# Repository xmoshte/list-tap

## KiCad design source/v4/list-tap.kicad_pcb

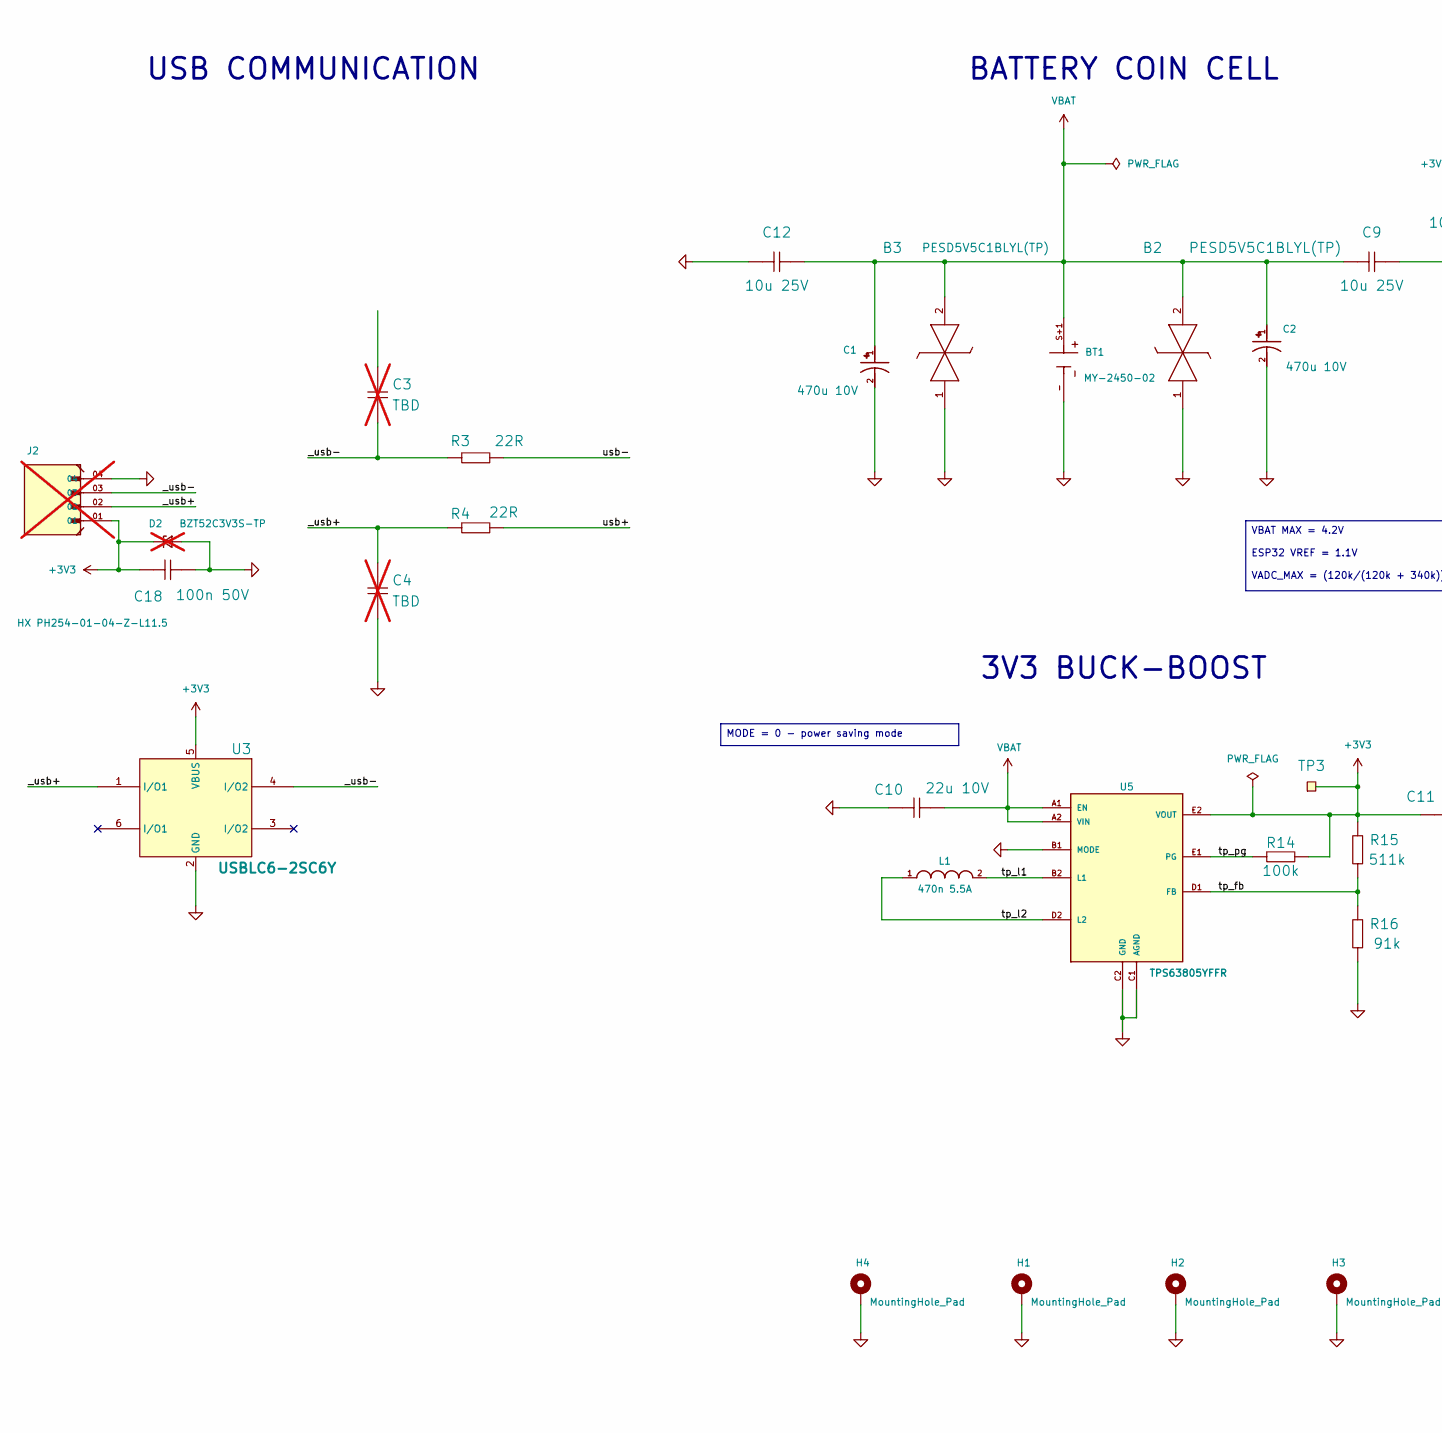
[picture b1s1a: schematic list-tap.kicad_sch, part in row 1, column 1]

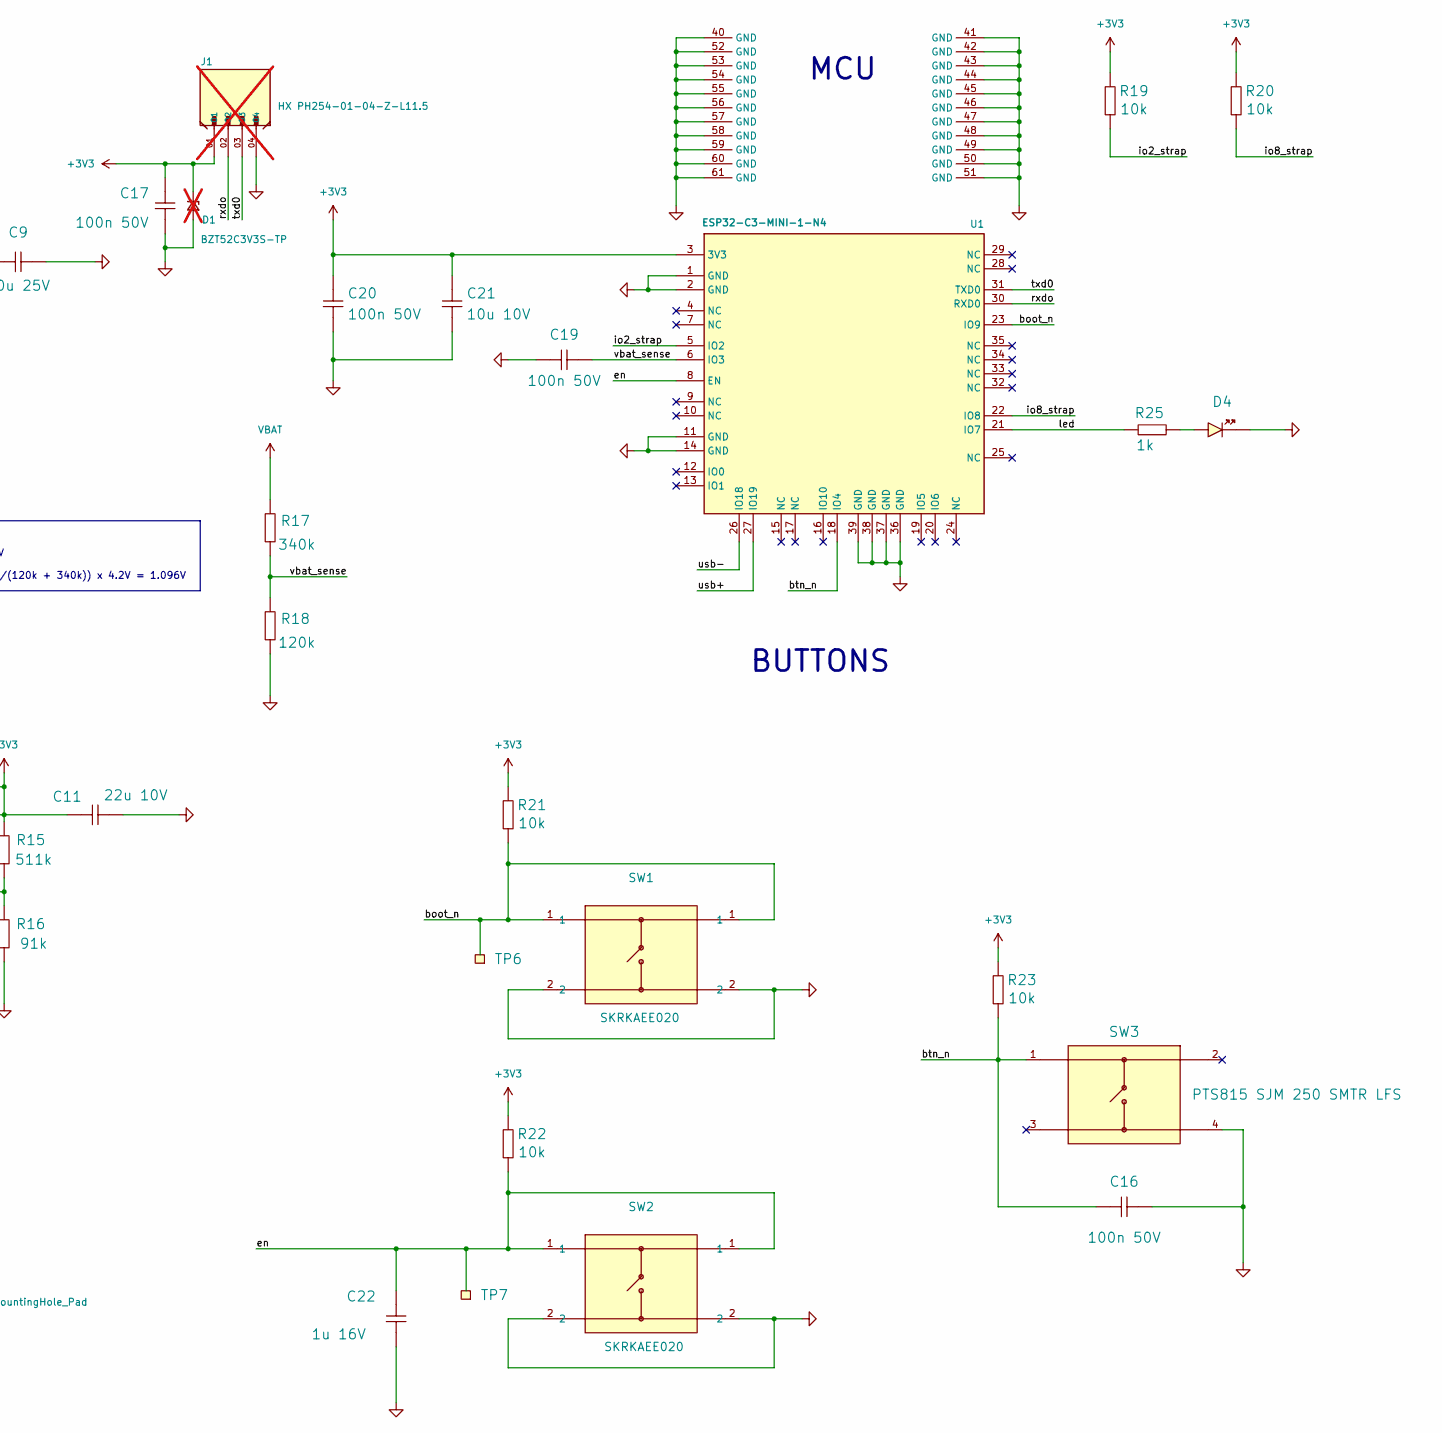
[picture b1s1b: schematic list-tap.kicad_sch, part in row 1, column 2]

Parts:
B2, B3: PESD5V5C1BLYL(TP); PESD5V5C1BLYL; Manufacturer Part Number PESD5V5C1BLYL(TP); LCSC Part # C54194967
BT1: MY-2450-02; BAT_BK-880; Manufacturer Part Number MY-2450-02; LCSC Part # C2979177
C1, C2: 470u 10V; PXTE010M477E060STU; Manufacturer Part Number PXTE010M477E060STU; LCSC Part # C724264
C3, C4: TBD; CAPC1005X04L; not fitted
C9, C12: 10u 25V; CAPC1608X06L; Manufacturer Part Number CL10A106MA8NRNC; LCSC Part # C96446
C10, C11: 22u 10V; CAPC1005X04L; Manufacturer Part Number CGA0402X5R226M100GT; LCSC Part # C6119813
C16, C17, C18, C19, C20: 100n 50V; CAPC1005X04L; Manufacturer Part Number CC0402X7R50V104MN; LCSC Part # C53084453
C21: 10u 10V; CAPC1005X04L; Manufacturer Part Number CL05A106MP5NUNC; LCSC Part # C315248
C22: 1u 16V; CAPC1005X04L; Manufacturer Part Number CL05A105KO5NNNC; LCSC Part # C29266
D1, D2: BZT52C3V3S-TP; SOD2512X115N; Manufacturer Part Number BZT52C3V3S-TP; LCSC Part # C668900; not fitted
D4: GREEN; LED_0402_GREEN; Manufacturer Part Number 16-213/GHC-YR1S1/3T; LCSC Part # C74338
H1, H2, H3, H4: MountingHole_Pad; MountingHole_2.2mm_M2_Pad_Via
J1, J2: HX PH254-01-04-Z-L11.5; Manufacturer Part Number HX PH254-01-04-Z-L11.5; LCSC Part # C52016392; not fitted
L1: 470n 5.5A; INDC2520X100N; Manufacturer Part Number PCT252010-R47-M; LCSC Part # C54557079
R3, R4: 22R; RESC1005X04L; Manufacturer Part Number RC0402FR-0722RL; LCSC Part # C114765
R14: 100k; RESC1005X04L; Manufacturer Part Number RC0402FR-07100KL; LCSC Part # C60491
R15: 511k; RESC1005X04L; Manufacturer Part Number 0402WGF5113TCE; LCSC Part # C64042
R16: 91k; RESC1005X04L; Manufacturer Part Number RT0402BRD0791KL; LCSC Part # C852952
R17: 340k; RESC1005X04L; Manufacturer Part Number FRC0402F3403TS; LCSC Part # C2933090
R18: 120k; RESC1005X04L; Manufacturer Part Number FRC0402F1203TS; LCSC Part # C2909314
R19, R20, R21, R22, R23: 10k; RESC1005X04L; Manufacturer Part Number RC0402FR-0710KL; LCSC Part # C60490
R25: 1k; RESC1005X04L; Manufacturer Part Number RC0402FR-071KL; LCSC Part # C106235
SW1, SW2: SKRKAEE020; SW2_SKRKAEE020_ALPS; Manufacturer Part Number SKRKAEE020; LCSC Part # C115357
SW3: PTS815 SJM 250 SMTR LFS; PTS815; Manufacturer Part Number PTS815 SJM 250 SMTR LFS; LCSC Part # C2689510
TP3, TP6, TP7: Test Point; TP_SMD_D1.5mm; Part Number TP_SMD_Ø1.5MM
U1: ESP32-C3-MINI-1-N4; ESP32C3MINI1N4; Manufacturer Part Number ESP32-C3-MINI-1-N4; LCSC Part # C2838502
U3: USBLC6-2SC6Y; SOT23-6L_STM; Manufacturer Part Number USBLC6-2SC6Y; LCSC Part # C2969755
U5: TPS63805YFFR; BGA15N40P5X3_225X134X62N; Manufacturer Part Number TPS63805YFFR; LCSC Part # C2879615

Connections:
+3V3: C11.1, C17.2, C18.2, C20.2, C21.2, D1.K, D2.K, J1.01, J2.01, R14.2, R15.2, R19.2, R20.2, R21.2, R22.2, R23.2, TP3.1 (1_1), U1.3 (3V3), U3.5 (VBUS), U5.E2 (VOUT), U5.E3 (VOUT)
/_usb+: C4.2, J2.02, R4.1, U3.1 (I/O1)
/_usb-: C3.1 (1_1), J2.03, R3.1, U3.4 (I/O2)
/boot_n: R21.1, SW1.1, TP6.1 (1_1), U1.23 (IO9)
/btn_n: C16.2, R23.1, SW3.1, U1.18 (IO4)
/en: C22.1, R22.1, SW2.1, TP7.1 (1_1), U1.8 (EN)
/io2_strap: R19.1, U1.5 (IO2)
/io8_strap: R20.1, U1.22 (IO8)
/led: R25.2, U1.21 (IO7)
/rxdo: J1.02, U1.30 (RXD0)
/tp_fb: R15.1, R16.2, U5.D1 (FB)
/tp_l1: L1.2, U5.B2 (L1), U5.B3 (L1)
/tp_l2: L1.1, U5.D2 (L2), U5.D3 (L2)
/tp_pg: R14.1, U5.E1 (PG)
/txd0: J1.03, U1.31 (TXD0)
/usb+: R4.2, U1.27 (IO19)
/usb-: R3.2, U1.26 (IO18)
/vbat_sense: C19.2, R17.1, R18.2, U1.6 (IO3)
GND: B2.1 (K1), B3.1 (K1), BT1.-, C1.2, C2.2, C4.1, C9.2, C10.1, C11.2, C12.2, C16.1, C17.1, C18.1, C19.1, C20.1, C21.1, C22.2, D1.A, D2.A, D4.K, H1.1 (1_1), H2.1 (1_1), H3.1 (1_1), H4.1 (1_1), J1.04, J2.04, R16.1, R18.1, SW1.2, SW2.2, SW3.4, U1.1 (GND), U1.2 (GND), U1.11 (GND), U1.14 (GND), U1.36 (GND), U1.37 (GND), U1.38 (GND), U1.39 (GND), U1.40 (GND), U1.41 (GND), U1.42 (GND), U1.43 (GND), U1.44 (GND), U1.45 (GND), U1.46 (GND), U1.47 (GND), U1.48 (GND), U1.49 (GND), U1.50 (GND), U1.51 (GND), U1.52 (GND), U1.53 (GND), U1.54 (GND), U1.55 (GND), U1.56 (GND), U1.57 (GND), U1.58 (GND), U1.59 (GND), U1.60 (GND), U1.61 (GND), U3.2 (GND), U5.B1 (MODE), U5.C1 (AGND), U5.C2 (GND), U5.C3 (GND)
unnamed: D4.A, R25.1
VBAT: B2.2 (K2), B3.2 (K2), BT1.S+1, BT1.S+2, C1.1, C2.1, C9.1, C10.2, C12.1, R17.2, U5.A1 (EN), U5.A2 (VIN), U5.A3 (VIN)

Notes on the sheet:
3V3 BUCK-BOOST
USB COMMUNICATION
MCU
BUTTONS
BATTERY COIN CELL
VBAT MAX = 4.2V ESP32 VREF = 1.1V VADC_MAX = (120k/(120k + 340k)) x 4.2V = 1.096V
MODE = 0 - power saving mode

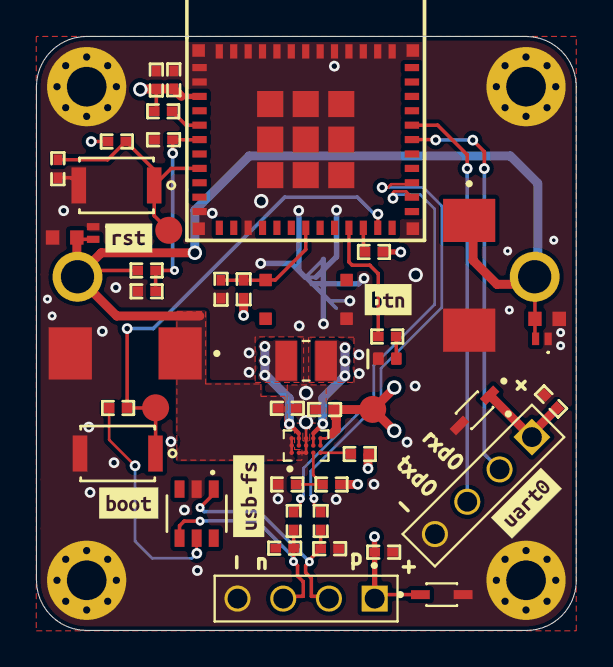
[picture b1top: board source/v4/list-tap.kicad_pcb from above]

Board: 2 copper layers, 30.0 x 33.0 mm, 55 parts (1 on the bottom side), 21 nets.

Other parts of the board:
kibuzzard-6AE057E3: G***; kibuzzard-6AE057E3
kibuzzard-6AE057F3: G***; kibuzzard-6AE057F3
kibuzzard-6AE0575D: G***; kibuzzard-6AE0575D
kibuzzard-6AE0576D: G***; kibuzzard-6AE0576D
kibuzzard-6AE0579C: G***; kibuzzard-6AE0579C

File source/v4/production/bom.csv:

Designator,Footprint,Quantity,Value,LCSC Part #
"B2, B3",PESD5V5C1BLYL,2,PESD5V5C1BLYL(TP),C54194967
BT1,BAT_BK-880,1,MY-2450-02,C2979177
"C1, C2",PXTE010M477E060STU,2,470u 10V,C724264
"C10, C11",CAPC1005X04L,2,22u 10V,C6119813
"C12, C9",CAPC1608X06L,2,10u 25V,C96446
"C16, C17, C18, C19, C20",CAPC1005X04L,5,100n 50V,C53084453
C21,CAPC1005X04L,1,10u 10V,C315248
C22,CAPC1005X04L,1,1u 16V,C29266
D4,LED_0402_GREEN,1,GREEN,C74338
L1,INDC2520X100N,1,470n 5.5A,C54557079
R14,RESC1005X04L,1,100k,C60491
R15,RESC1005X04L,1,511k,C64042
R16,RESC1005X04L,1,91k,C852952
R17,RESC1005X04L,1,340k,C2933090
R18,RESC1005X04L,1,120k,C2909314
"R19, R20, R21, R22, R23",RESC1005X04L,5,10k,C60490
R25,RESC1005X04L,1,1k,C106235
"R3, R4",RESC1005X04L,2,22R,C114765
"SW1, SW2",SW2_SKRKAEE020_ALPS,2,SKRKAEE020,C115357
SW3,PTS815,1,PTS815 SJM 250 SMTR LFS,C2689510
U1,ESP32C3MINI1N4,1,ESP32-C3-MINI-1-N4,C2838502
U3,SOT23-6L_STM,1,USBLC6-2SC6Y,C2969755
U5,BGA15N40P5X3_225X134X62N,1,TPS63805YFFR,C2879615

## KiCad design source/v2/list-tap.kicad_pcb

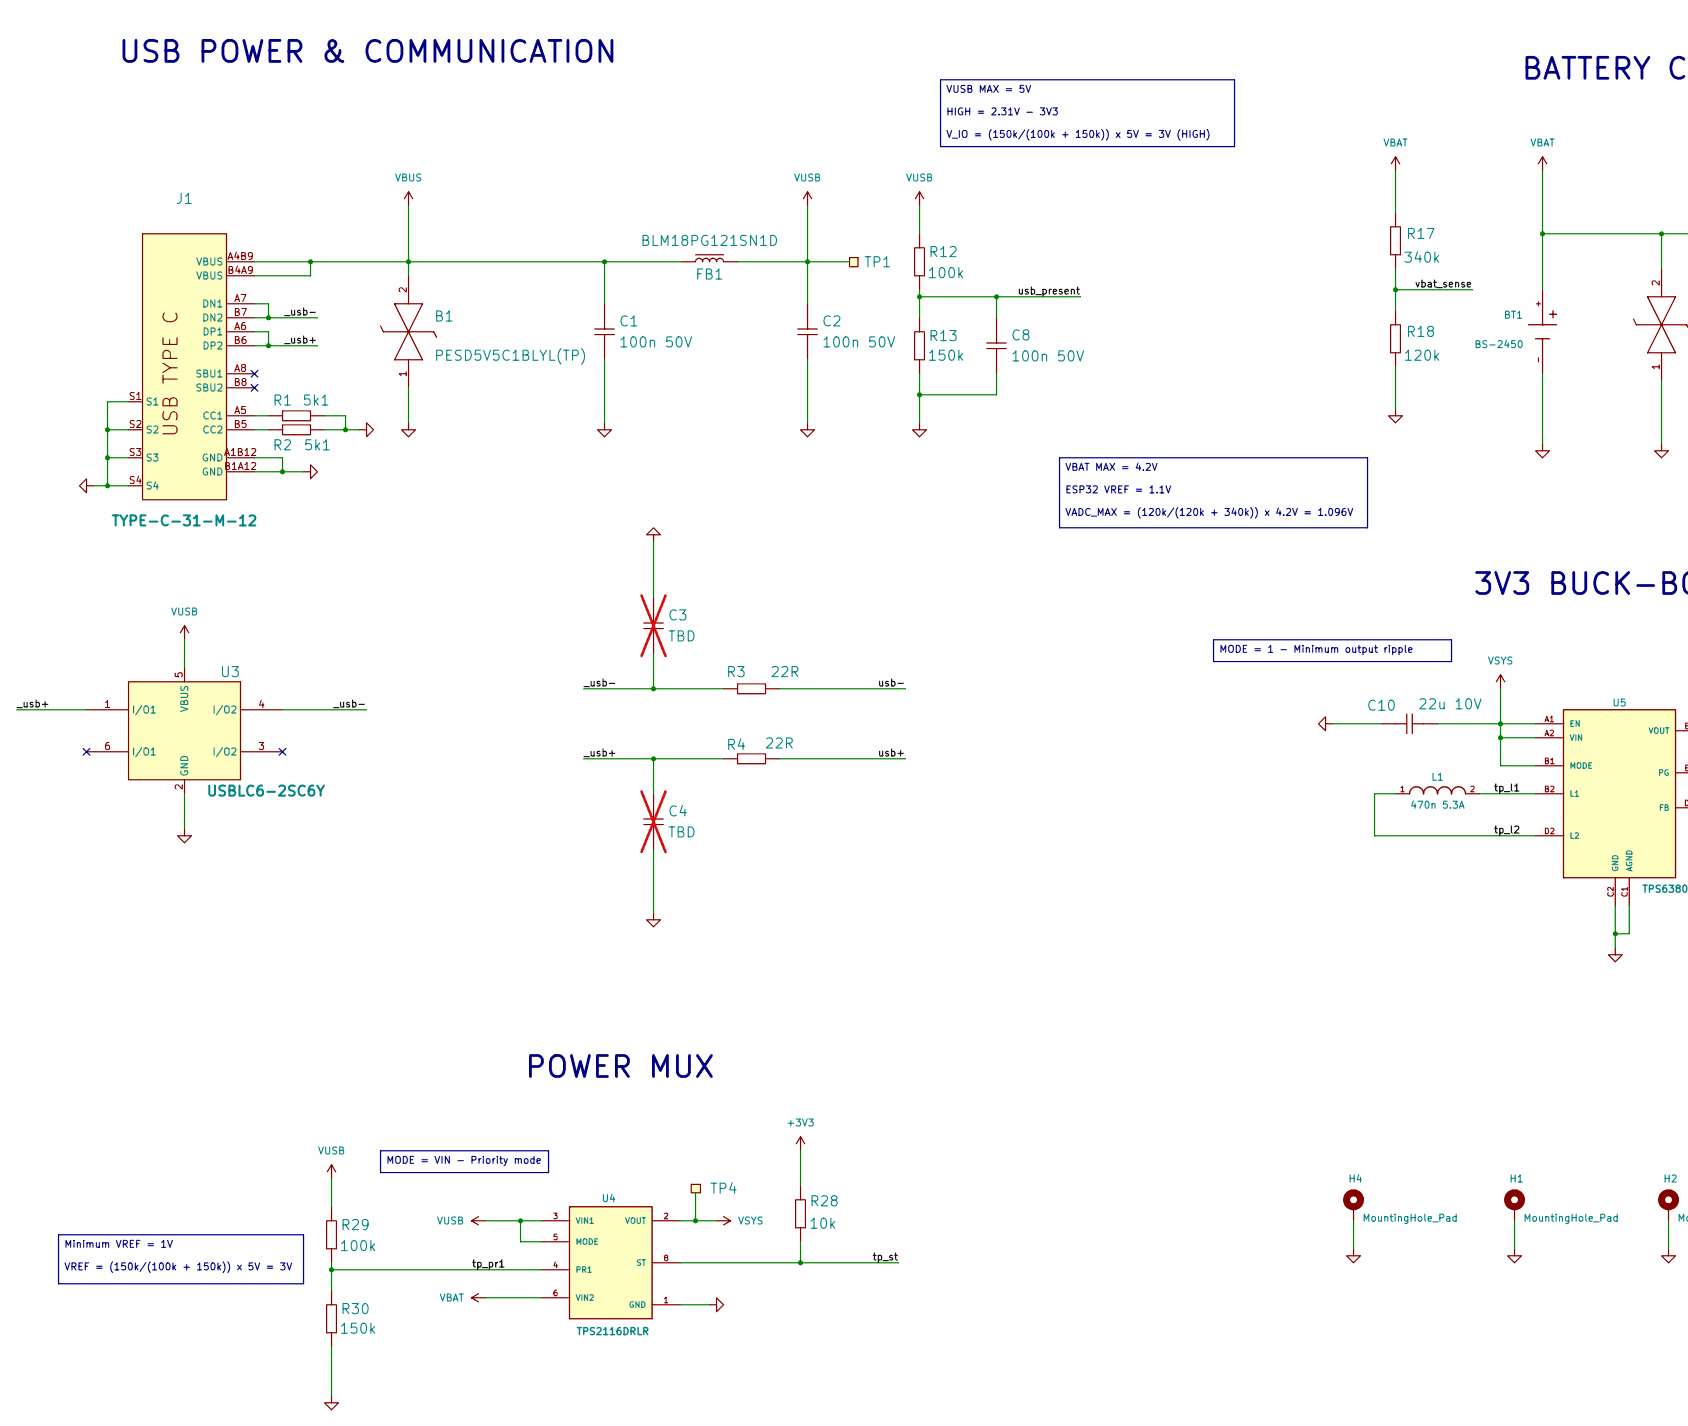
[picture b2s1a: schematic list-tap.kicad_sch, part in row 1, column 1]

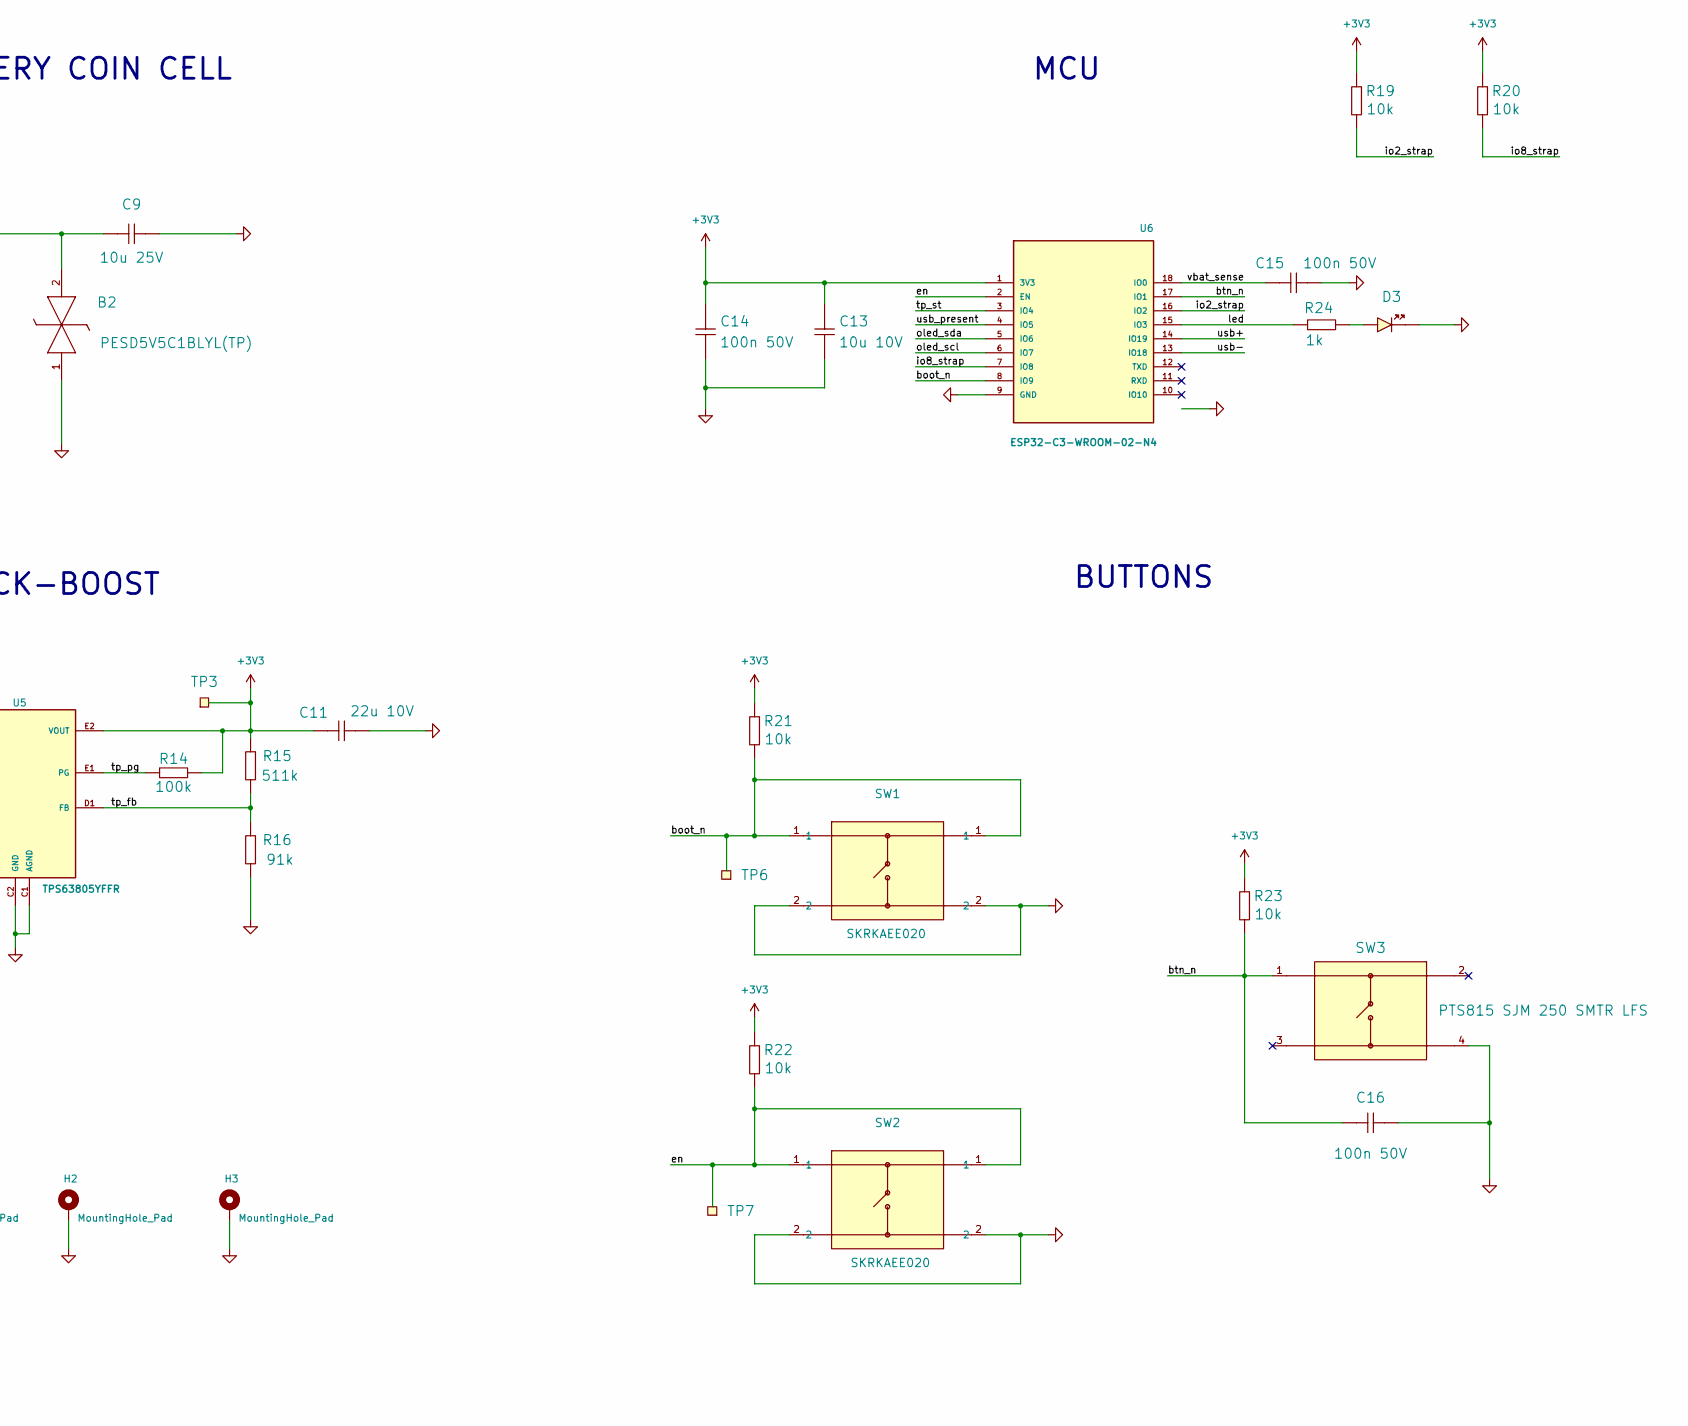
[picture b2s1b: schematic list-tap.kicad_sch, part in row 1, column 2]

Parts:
B1, B2: PESD5V5C1BLYL(TP); PESD5V5C1BLYL; Manufacturer Part Number PESD5V5C1BLYL(TP); LCSC Part # C54194967
BT1: BS-2450; BAT_BS-2450; Manufacturer Part Number BS-2450; LCSC Part # C5955421
C1, C2, C8, C14, C15, C16: 100n 50V; CAPC1005X04L; Manufacturer Part Number CC0402X7R50V104MN; LCSC Part # C53084453
C3, C4: TBD; CAPC1005X04L; not fitted
C9: 10u 25V; CAPC1608X06L; Manufacturer Part Number CL10A106MA8NRNC; LCSC Part # C96446
C10, C11: 22u 10V; CAPC1005X04L; Manufacturer Part Number CGA0402X5R226M100GT; LCSC Part # C6119813
C13: 10u 10V; CAPC1005X04L; Manufacturer Part Number CL05A106MP5NUNC; LCSC Part # C315248
D3: GREEN; LED_0402_GREEN; Manufacturer Part Number 16-213/GHC-YR1S1/3T; LCSC Part # C74338
FB1: BLM18PG121SN1D; FB_0603; Manufacturer Part Number BLM18PG121SN1D; LCSC Part # C14709
H1, H2, H3, H4: MountingHole_Pad; MountingHole_2.2mm_M2_Pad_Via
J1: TYPE-C-31-M-12; HRO_TYPE-C-31-M-12; Manufacturer Part Number TYPE-C-31-M-12; LCSC Part # C165948
L1: 470n 5.3A; INDC2520X100N; Manufacturer Part Number YSMC252008H-R47MB; LCSC Part # C46961980
R1, R2: 5k1; RESC1005X04L; Manufacturer Part Number RC0402FR-075K1L; LCSC Part # C105872
R3, R4: 22R; RESC1005X04L; Manufacturer Part Number RC0402FR-0722RL; LCSC Part # C114765
R12, R14, R29: 100k; RESC1005X04L; Manufacturer Part Number RC0402FR-07100KL; LCSC Part # C60491
R13, R30: 150k; RESC1005X04L; Manufacturer Part Number FRC0402F1503TS; LCSC Part # C2909320
R15: 511k; RESC1005X04L; Manufacturer Part Number 0402WGF5113TCE; LCSC Part # C64042
R16: 91k; RESC1005X04L; Manufacturer Part Number RT0402BRD0791KL; LCSC Part # C852952
R17: 340k; RESC1005X04L; Manufacturer Part Number FRC0402F3403TS; LCSC Part # C2933090
R18: 120k; RESC1005X04L; Manufacturer Part Number FRC0402F1203TS; LCSC Part # C2909314
R19, R20, R21, R22, R23, R28: 10k; RESC1005X04L; Manufacturer Part Number RC0402FR-0710KL; LCSC Part # C60490
R24: 1k; RESC1005X04L; Manufacturer Part Number RC0402FR-071KL; LCSC Part # C106235
SW1, SW2: SKRKAEE020; SW2_SKRKAEE020_ALPS; Manufacturer Part Number SKRKAEE020; LCSC Part # C115357
SW3: PTS815 SJM 250 SMTR LFS; PTS815; Manufacturer Part Number PTS815 SJM 250 SMTR LFS; LCSC Part # C2689510
TP1, TP3, TP4, TP6, TP7: Test Point; TP_SMD_D1.5mm; Part Number TP_SMD_Ø1.5MM
U3: USBLC6-2SC6Y; SOT23-6L_STM; Manufacturer Part Number USBLC6-2SC6Y; LCSC Part # C2969755
U4: TPS2116DRLR; SOTFL50P160X60-8N; Manufacturer Part Number TPS2116DRLR; LCSC Part # C3235557
U5: TPS63805YFFR; BGA15N40P5X3_225X134X62N; Manufacturer Part Number TPS63805YFFR; LCSC Part # C2879615
U6: ESP32-C3-WROOM-02-N4; MODULE_ESP32-C3-WROOM-02-H4; Manufacturer Part Number ESP32-C3-WROOM-02-N4; LCSC Part # C2934560

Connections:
+3V3: C11.1, C13.2, C14.2, R14.2, R15.2, R19.2, R20.2, R21.2, R22.2, R23.2, R28.2, TP3.1 (1_1), U5.E2 (VOUT), U5.E3 (VOUT), U6.1 (3V3)
/_usb+: C4.2, J1.A6 (DP1), J1.B6 (DP2), R4.1, U3.1 (I/O1)
/_usb-: C3.1, J1.A7 (DN1), J1.B7 (DN2), R3.1, U3.4 (I/O2)
/boot_n: R21.1, SW1.1, TP6.1 (1_1), U6.8 (IO9)
/btn_n: C16.2, R23.1, SW3.1, U6.17 (IO1)
/en: R22.1, SW2.1, TP7.1 (1_1), U6.2 (EN)
/io2_strap: R19.1, U6.16 (IO2)
/io8_strap: R20.1, U6.7 (IO8)
/led: R24.2, U6.15 (IO3)
/oled_scl: U6.6 (IO7)
/oled_sda: U6.5 (IO6)
/tp_fb: R15.1, R16.2, U5.D1 (FB)
/tp_l1: L1.2, U5.B2 (L1), U5.B3 (L1)
/tp_l2: L1.1, U5.D2 (L2), U5.D3 (L2)
/tp_pg: R14.1, U5.E1 (PG)
/tp_pr1: R29.1, R30.2, U4.4 (PR1)
/tp_st: R28.1, U4.8 (ST), U6.3 (IO4)
/usb+: R4.2, U6.14 (IO19)
/usb-: R3.2, U6.13 (IO18)
/usb_present: C8.2, R12.1, R13.2, U6.4 (IO5)
/vbat_sense: C15.2, R17.1, R18.2, U6.18 (IO0)
GND: B1.1 (K1), B2.1 (K1), BT1.-, C1.1, C2.1, C3.2, C4.1, C8.1, C9.2, C10.1, C11.2, C13.1, C14.1, C15.1, C16.1, D3.K, H1.1 (1_1), H2.1 (1_1), H3.1 (1_1), H4.1 (1_1), J1.A1B12 (GND), J1.B1A12 (GND), J1.S1, J1.S2, J1.S3, J1.S4, R1.2, R2.2, R13.1, R16.1, R18.1, R30.1, SW1.2, SW2.2, SW3.4, U3.2 (GND), U4.1 (GND), U5.C1 (AGND), U5.C2 (GND), U5.C3 (GND), U6.9 (GND), U6.19 (GND), U6.20 (GND), U6.21 (GND), U6.22 (GND), U6.23 (GND), U6.24 (GND), U6.25 (GND), U6.26 (GND), U6.27 (GND), U6.28 (GND), U6.29 (GND), U6.30 (GND), U6.31 (GND), U6.32 (GND), U6.33 (GND), U6.34 (GND), U6.35 (GND), U6.36 (GND), U6.37 (GND), U6.38 (GND), U6.39 (GND)
unnamed: D3.A, R24.1
unnamed: J1.A5 (CC1), R1.1
unnamed: J1.B5 (CC2), R2.1
VBAT: B2.2 (K2), BT1.+, C9.1, R17.2, U4.6 (VIN2)
VBUS: B1.2 (K2), C1.2, FB1.1, J1.A4B9 (VBUS), J1.B4A9 (VBUS)
VSYS: C10.2, TP4.1 (1_1), U4.2 (VOUT), U4.7 (VOUT), U5.A1 (EN), U5.A2 (VIN), U5.A3 (VIN), U5.B1 (MODE)
VUSB: C2.2, FB1.2, R12.2, R29.2, TP1.1 (1_1), U3.5 (VBUS), U4.3 (VIN1), U4.5 (MODE)

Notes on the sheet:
3V3 BUCK-BOOST
MCU
USB POWER & COMMUNICATION
BUTTONS
POWER MUX
BATTERY COIN CELL
VUSB MAX = 5V HIGH = 2.31V - 3V3 V_IO = (150k/(100k + 150k)) x 5V = 3V (HIGH)
VBAT MAX = 4.2V ESP32 VREF = 1.1V VADC_MAX = (120k/(120k + 340k)) x 4.2V = 1.096V
MODE = 1 - Minimum output ripple
Minimum VREF = 1V VREF = (150k/(100k + 150k)) x 5V = 3V
MODE = VIN - Priority mode

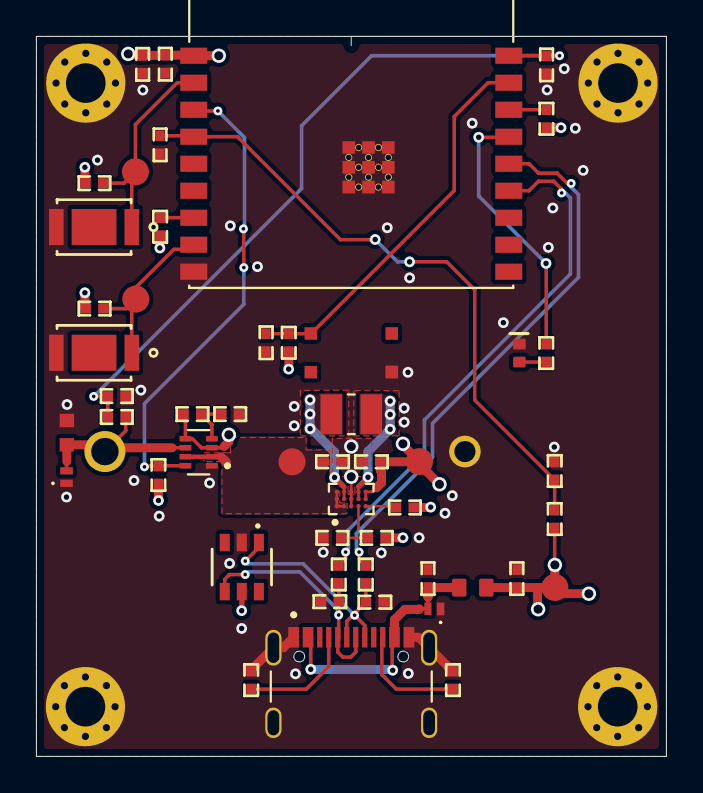
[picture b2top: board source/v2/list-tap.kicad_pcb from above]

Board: 4 copper layers, 35.0 x 40.0 mm, 55 parts (1 on the bottom side), 27 nets.

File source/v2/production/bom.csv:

"Reference","Value","Description","Manufacturer Part Number","LCSC Part #","Qty"
"U3","USBLC6-2SC6Y","Automotive very low capacitance ESD protection","USBLC6-2SC6Y","C2969755","1"
"J1","TYPE-C-31-M-12","USB Type C Connector Horizontal SMT","TYPE-C-31-M-12","C165948","1"
"U5","TPS63805YFFR","2-A, high-efficient, 11-µA quiescent current buck-boost converter with tiny solution size","TPS63805YFFR","C2879615","1"
"U4","TPS2116DRLR","1.6-V to 5.5-V, 40-mΩ, 2.5-A, low-IQ, priority power multiplexer","TPS2116DRLR","C3235557","1"
"SW1,SW2","SKRKAEE020","Tactile Switch SPST-NO Top Actuated Surface Mount","SKRKAEE020","C115357","2"
"SW3","PTS815 SJM 250 SMTR LFS","Tactile Switches Tact Switch, 12 VDC, 50 mA, 4.2x3.2, 2.5mm H, 180gf, J leadspp SPST","PTS815 SJM 250 SMTR LFS","C2689510","1"
"U1","PM2.54-1x4PZZ-H5.7","4 Position Header Connector 0.100 (2.54mm) Through Hole Gold","PM2.54-1x4PZZ-H5.7","C55218874","1"
"B1,B2","PESD5V5C1BLYL(TP)","PESD5V5C1BL - Extremely low clamping bidirectional ESD protection diode@en-us","PESD5V5C1BLYL(TP)","C54194967","2"
"D3","GREEN","LED 0402 GREEN SMD","16-213/GHC-YR1S1/3T","C74338","1"
"U6","ESP32-C3-WROOM-02-N4","WiFi Modules (802.11) (Engineering Samples) SMD module, ESP32-C3, 4MB SPI flash, PCB antenna, -40 C +85 C","ESP32-C3-WROOM-02-N4","C2934560","1"
"BT1","BS-2450","Battery Holder (Open) Coin, 24.5mm 1 Cell PC Pin","BS-2450","C5955421","1"
"FB1","BLM18PG121SN1D","Ferrite Bead SMD 0603","BLM18PG121SN1D","C14709","1"
"L1","470n 5.3A","Inductors, Fixed, 1.5uH 1MHz 20% | Bourns CVH252009-1R5M","YSMC252008H-R47MB","C46961980","1"
"C10,C11","22u 10V","Capacitor Ceramic 0402","CGA0402X5R226M100GT","C6119813","2"
"C9","10u 25V","Capacitor Ceramic 0603","CL10A106MA8NRNC","C96446","1"
"C13","10u 10V","Capacitor Ceramic 0402","CL05A106MP5NUNC","C315248","1"
"C1,C2,C8,C12,C14,C15,C16","100n 50V","Capacitor Ceramic 0402","CC0402X7R50V104MN","C53084453","7"
"R15","511k","Resistor Ceramic 0402","0402WGF5113TCE","C64042","1"
"R17","340k","Resistor Ceramic 0402","FRC0402F3403TS","C2933090","1"
"R13,R30","150k","Resistor Ceramic 0402","FRC0402F1503TS","C2909320","2"
"R18","120k","Resistor Ceramic 0402","FRC0402F1203TS","C2909314","1"
"R12,R14,R29","100k","Resistor Ceramic 0402","RC0402FR-07100KL","C60491","3"
"R16","91k","Resistor Ceramic 0402","RT0402BRD0791KL","C852952","1"
"R19,R20,R21,R22,R23,R28","10k","Resistor Ceramic 0402","RC0402FR-0710KL","C60490","6"
"R1,R2","5k1","Resistor Ceramic 0402","RC0402FR-075K1L","C105872","2"
"R25,R26","4k7","Resistor Ceramic 0402","RC0402FR-074K7L","C105871","2"
"R24","1k","Resistor Ceramic 0402","RC0402FR-071KL","C106235","1"
"R3,R4","22R","Resistor Ceramic 0402","RC0402FR-0722RL","C114765","2"
